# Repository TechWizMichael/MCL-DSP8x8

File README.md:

# MCL-DSP8x8
## Description
Audio Signal Processor based on ESP32-S3 and ADAU1452.

## Goals
+ Eight channels of analog audio input and output
+ Compatibility with "12V" automotive systems
  + As of v0.8 PCB, the device is powered using USB, so 12V operation will require an external USB or 5V power converter.
+ WIP: Remote control through ESP32 (Serial and basic controls through BLE).
+ WIP: Download and upload of settings to restore after flashing new firmware.

## Current State of Firmware
+ Bit of a mess. It's been changing as I've been messing with testing.
+ USB programming of ESP32 is functional.
+ ESP32 successfully programs ADAU1452 and AK4619VN.
+ Bluetooth functionality was briefly tested, with a generic BLE app on android controlling output gain.
+ Can choose between default and custom DSP program by commenting/uncommenting a line in the main .INO file.
  + Default DSP is linear mapping (pass-through) of input to output until ESP32 updates settings after flashing.
    + Defualt will be guaranteed to be compatible with remote control.
      + For this reason, it is highly recommended that the default DSP project, code, and headers remain unchanged.
  + Custom DSP is provided example with registers and input/outputs correctly mapped to physical connections.
    + The Custom DSP program can be modified, but will not offer remote control through the ESP32.
    + The Custom DSP "example" in this repository will likely be whatever I programmed last with it.

## Current state of hardware
### v0.8 (In Testing)
- Important: Buttons are connected incorrectly so they behave as though they are permanently pressed.
  - Removing the buttons or not getting them placed will fix the issue, but the relevant pins may need to be shorted for first-time flashing firmware.
- Using passive attenuation, input range can be expanded.
  - For example, a voltage divider consisting of 47k and 5.6k can be used to achieve 20dB attenuation.
- Analog inputs and outputs use pinheaders with 5 pins with 2.54mm pitch.
  - Each connector carries a differential/balanced connection for two channels.
  - GND, A+, A-, B+, B-
- Similar connectors offer connection to Multi-purpose and AUXADC pins on ADAU1452.
- All appears to be functional with minimal noise
- Measurements:
  - Measured Maximum output (10% THD): 0.939 Vrms (+1.7 dBu)
  - Measured Maximum output (1% THD): 0.814 Vrms (+0.4 dBu)
  - Measured Maximum Input (10% THD): 1.27 Vrms (+4.3 dBu) - Note: potentially my USB interface clipping at 1.28V
  - Measured maximum input (1% THD): 1 Vrms (+2.2dBu)

### Preview of v0.8 from JLCPCB

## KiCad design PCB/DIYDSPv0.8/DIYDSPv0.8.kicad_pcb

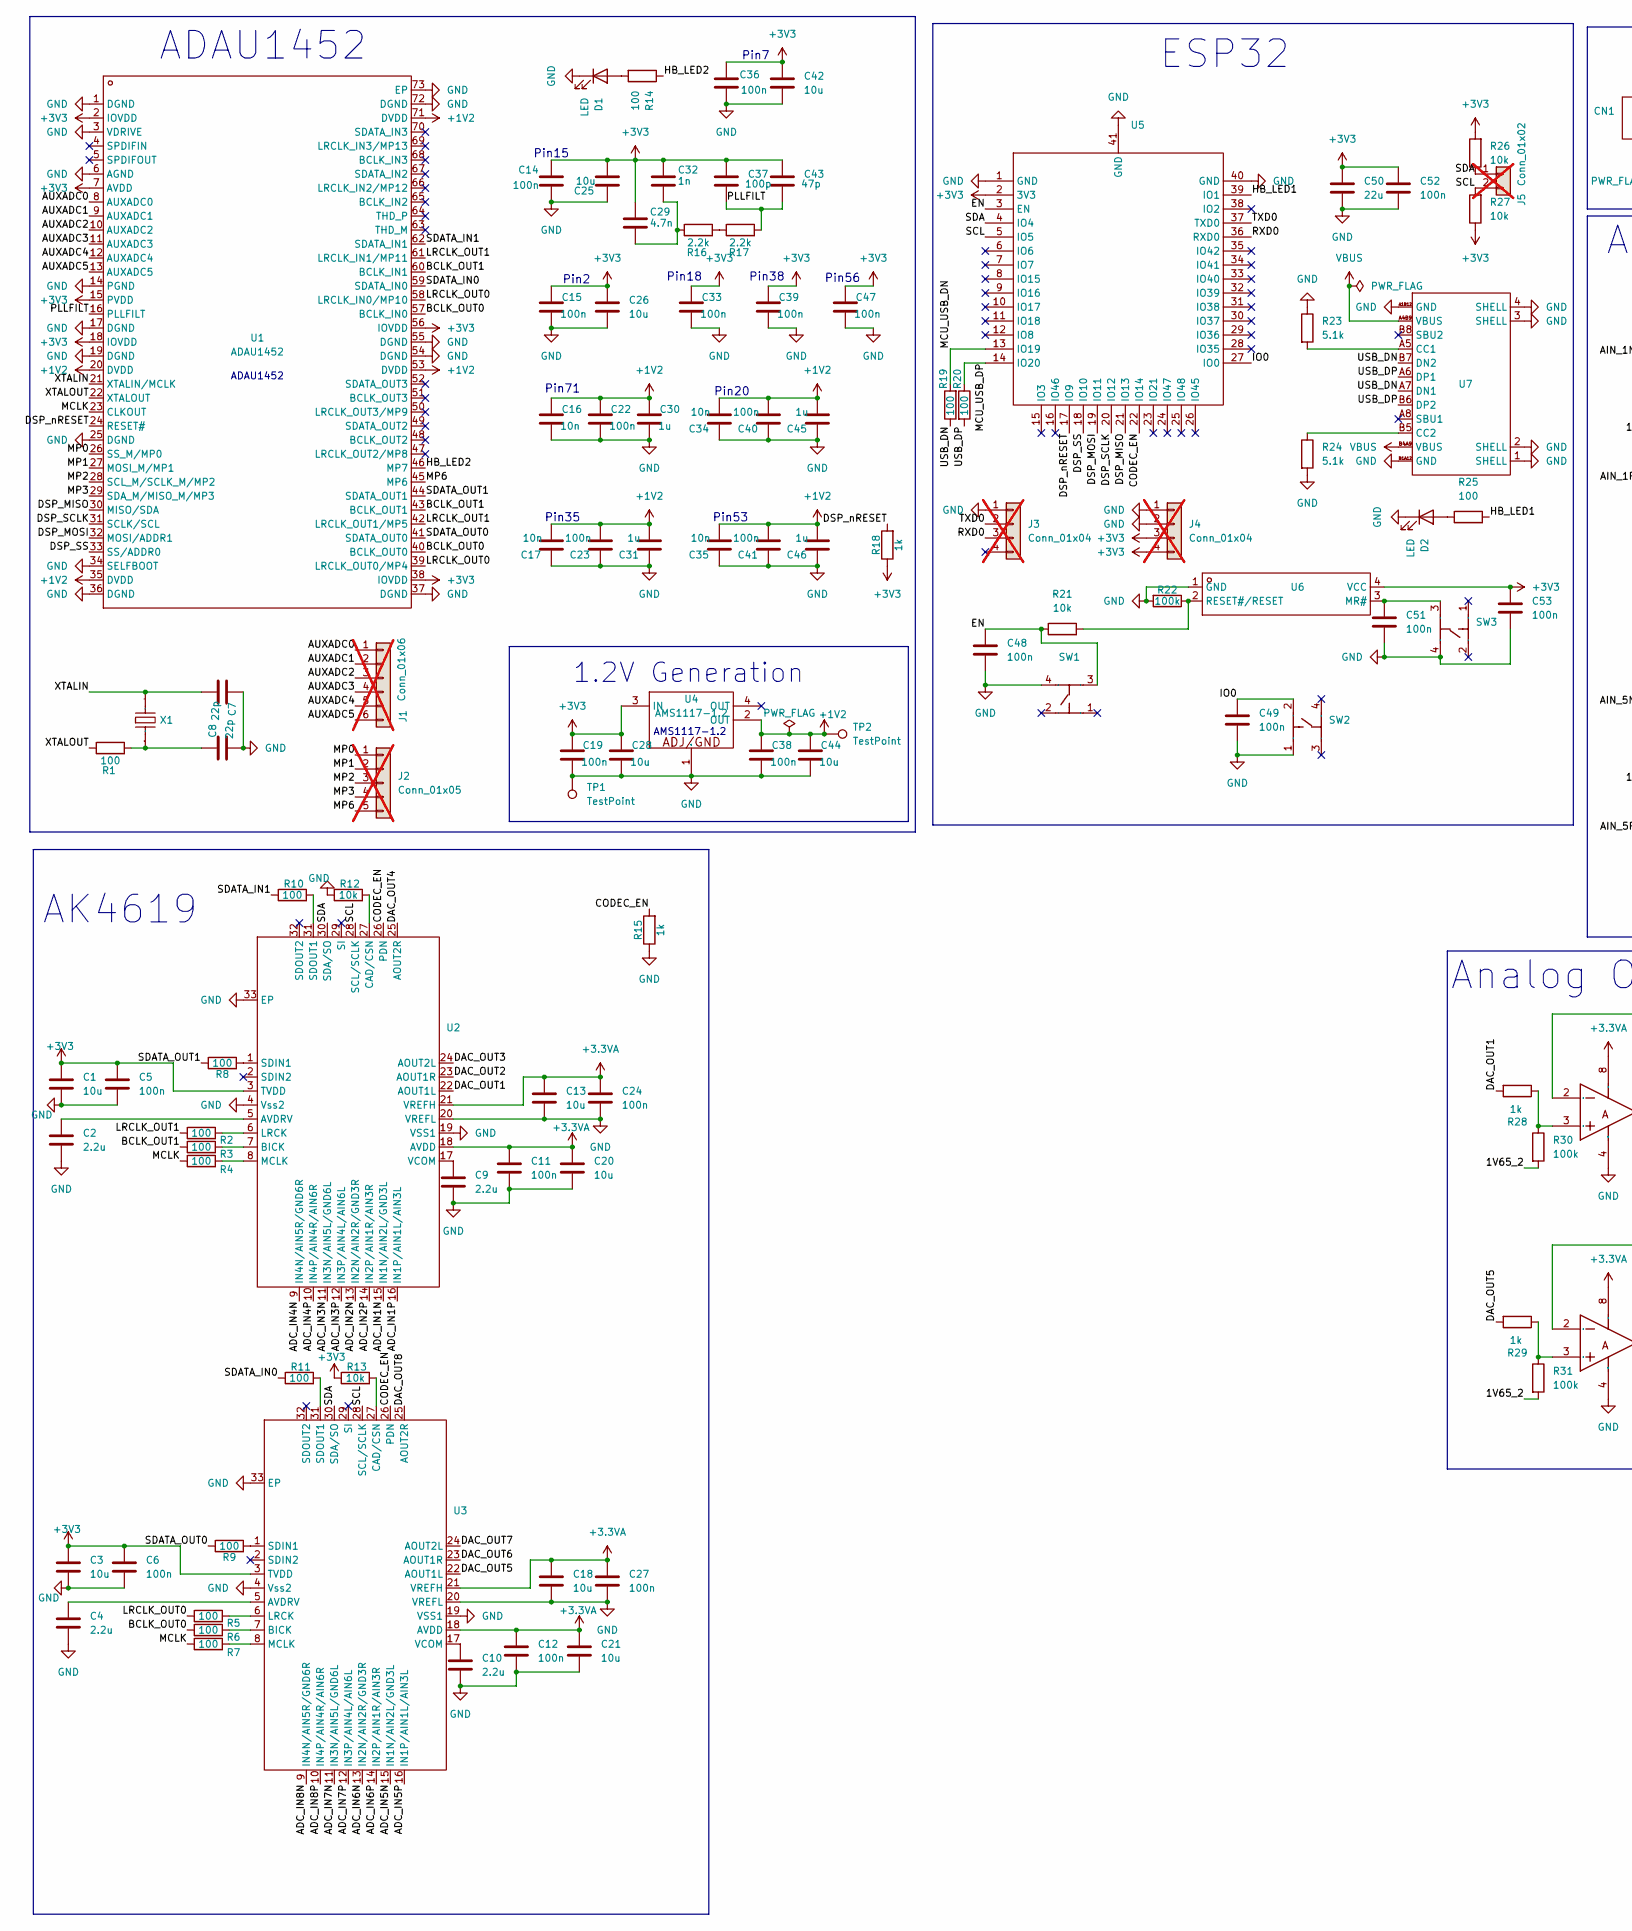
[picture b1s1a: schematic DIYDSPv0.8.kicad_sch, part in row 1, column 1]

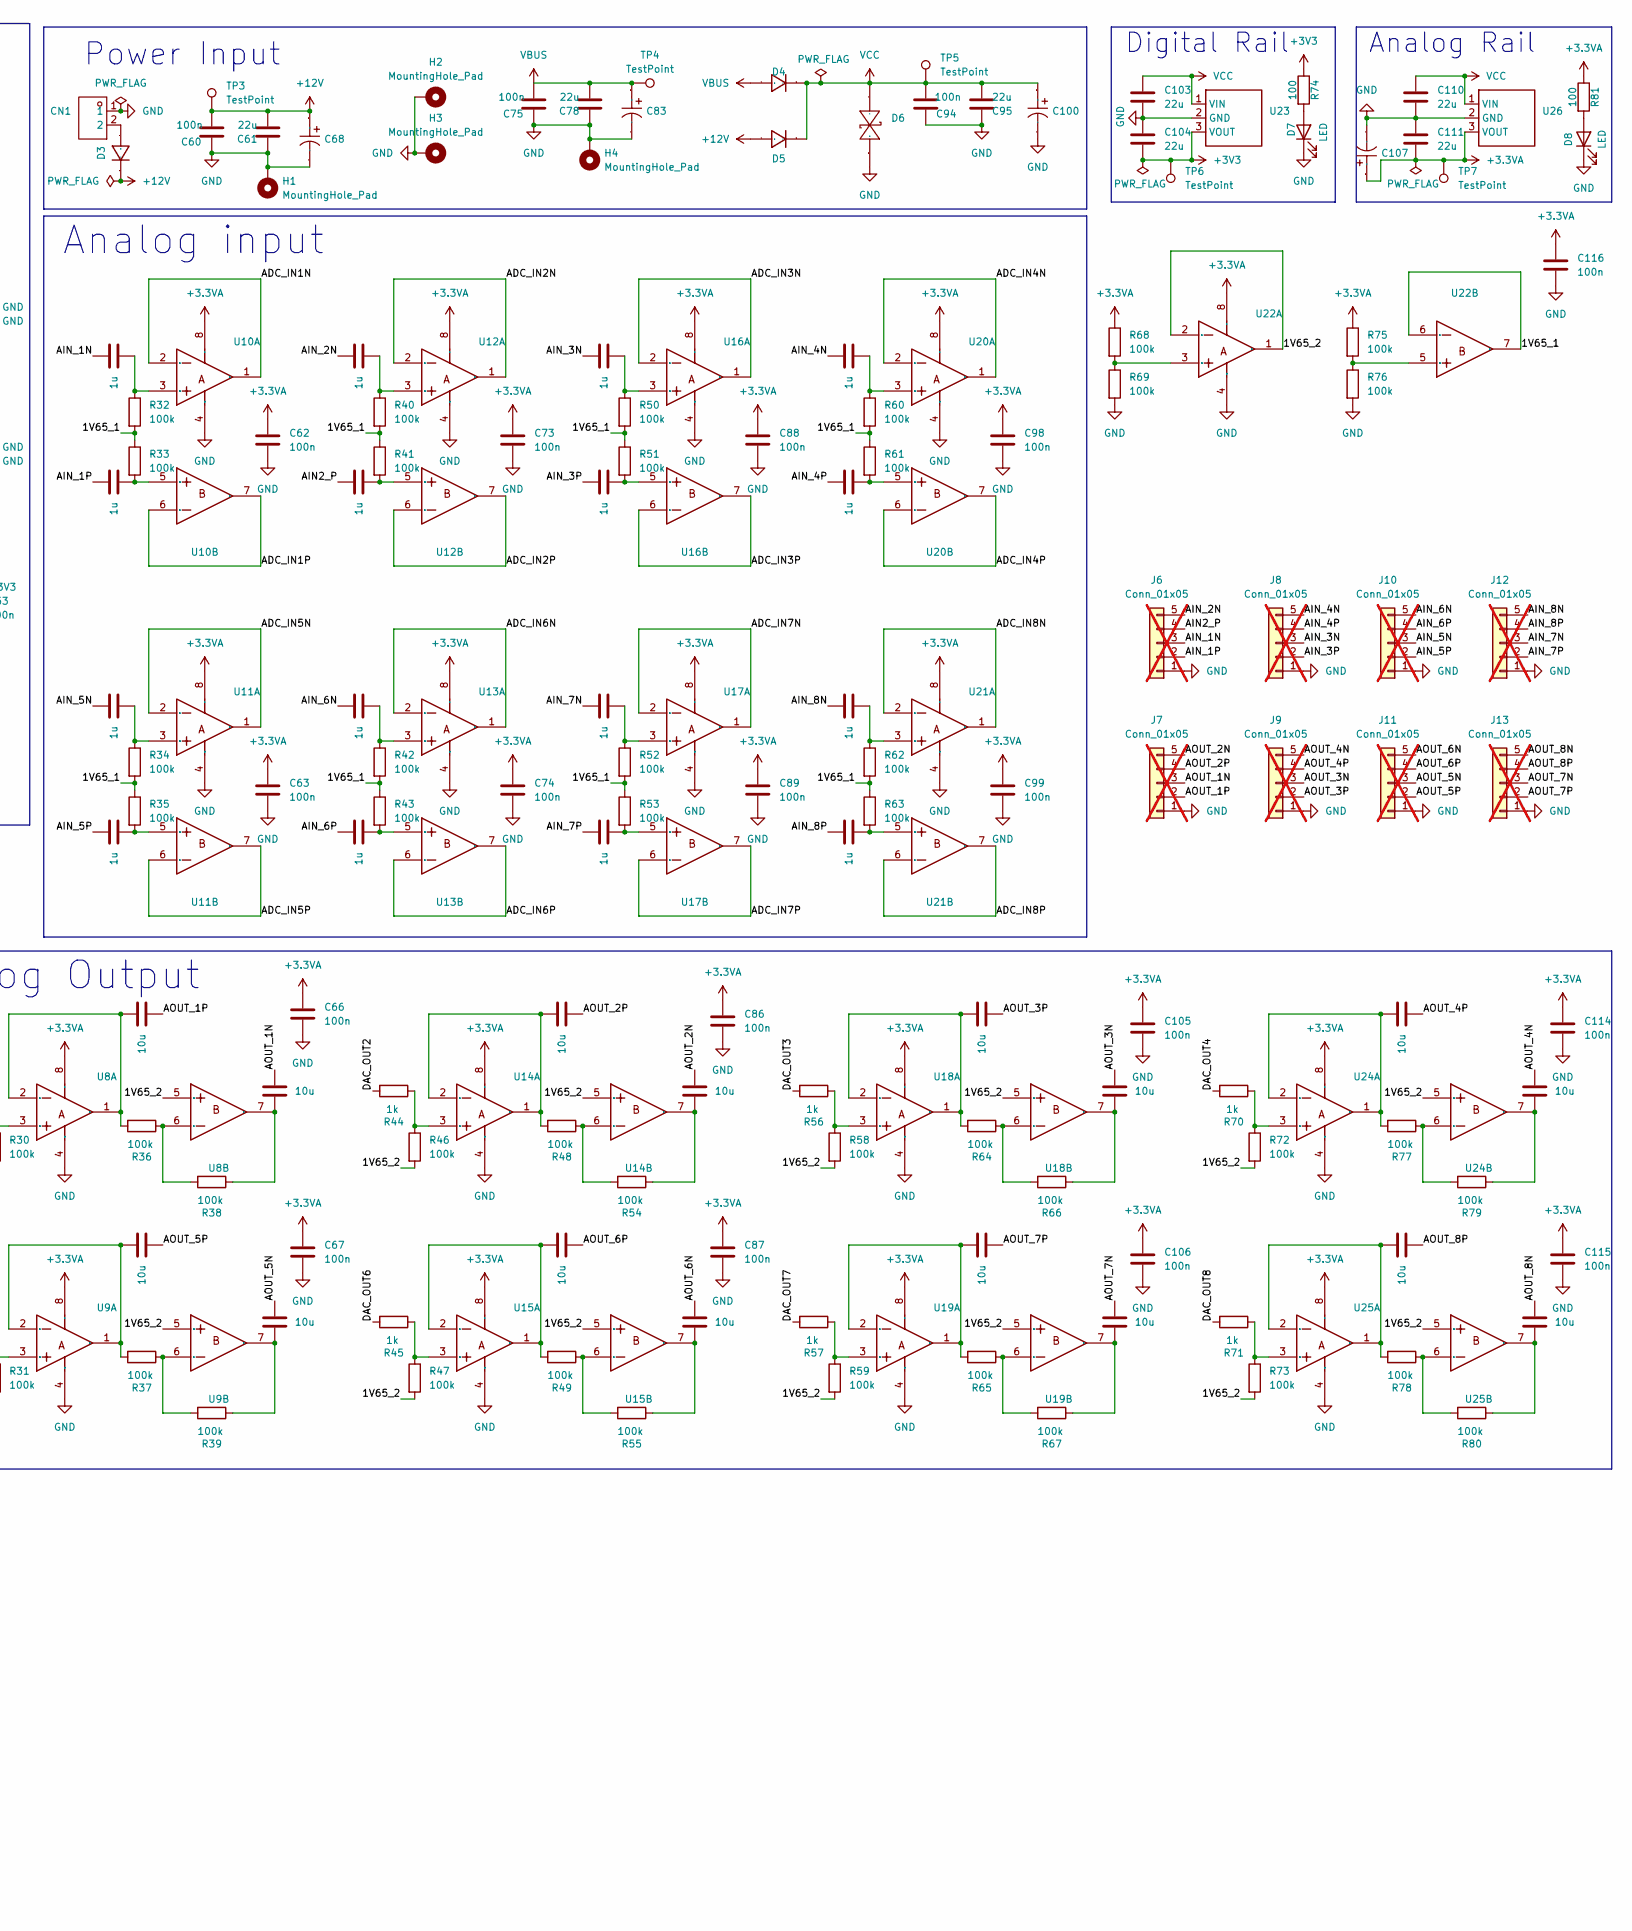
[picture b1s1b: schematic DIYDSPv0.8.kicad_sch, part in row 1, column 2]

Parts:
C1, C3, C13, C18, C20, C21, C25, C26, C28, C42, C44, C58, C59, C64, C65, C76, C77, C84, C85, C96, C97, C101, C102, C108, C109, C112, C113: 10u; C_0603_1608Metric; LCSC Part # C96446
C2, C4, C9, C10: 2.2u; C_0402_1005Metric; LCSC Part # C12530
C5, C6, C11, C12, C14, C15, C19, C22, C23, C24, C27, C33, C36, C38, C39, C40, C41, C47, C48, C49, C51, C52, C53, C60, C62, C63, C66, C67, C73, C74, C75, C86, C87, C88, C89, C94, C98, C99, C105, C106, C114, C115, C116: 100n; C_0402_1005Metric; LCSC Part # C307331
C7, C8: 22p; C_0402_1005Metric; LCSC Part # C1555
C16, C17, C34, C35: 10n; C_0402_1005Metric; LCSC Part # C15195
C29: 4.7n; C_0402_1005Metric; LCSC Part # C1538
C30, C31, C45, C46, C54, C55, C56, C57, C69, C70, C71, C72, C79, C80, C81, C82, C90, C91, C92, C93: 1u; C_0402_1005Metric; LCSC Part # C52923
C32: 1n; C_0402_1005Metric; LCSC Part # C1523
C37: 100p; C_0402_1005Metric; LCSC Part # C1546
C43: 47p; C_0402_1005Metric; LCSC Part # C1567
C50, C61, C78, C95, C103, C104, C110, C111: 22u; C_0805_2012Metric; LCSC Part # C45783
C68, C83, C100, C107: 220uF; RVT1V221M0810; Manufacturer Part RVT1V221M0810; LCSC Part Name 220uF ±20% 35V
CN1: MX126-5.0-02P-GN01-Cu-S-A; Manufacturer Part MX126-5.0-02P-GN01-Cu-S-A; LCSC Part Name 1x2P 5mm 直插 排数:1 每排P数:2
D1, D2, D7, D8: LED; LED_0805_2012Metric; LCSC Part # C84256
D3, D4, D5: CUS08F30,H3F; Manufacturer Part CUS08F30,H3F; LCSC Part Name 电压:30V 电流:800mA
D6: SMF20CA; Manufacturer Part SMF20CA; LCSC Part Name 双向TVS 20V截止 峰值浪涌电流：6.2A
H1, H2, H3, H4: MountingHole_Pad; MountingHole_3.2mm_M3_Pad_TopBottom
J1: Conn_01x06; PinHeader_1x06_P2.54mm_Vertical; not fitted
J2, J6, J7, J8, J9, J10, J11, J12, J13: Conn_01x05; PinHeader_1x05_P2.54mm_Vertical; not fitted
J3, J4: Conn_01x04; PinHeader_1x04_P2.54mm_Vertical; not fitted
J5: Conn_01x02; PinHeader_1x02_P2.54mm_Vertical; not fitted
R1, R2, R3, R4, R5, R6, R7, R8, R9, R10, R11, R14, R19, R20, R25, R74, R81: 100; R_0805_2012Metric; LCSC Part # C17408
R12, R13, R21, R26, R27: 10k; R_0402_1005Metric; LCSC Part # C25744
R15, R18, R28, R29, R44, R45, R56, R57, R70, R71: 1k; R_0402_1005Metric; LCSC Part # C11702
R16, R17: 2.2k; R_0402_1005Metric; LCSC Part # C25879
R22, R30, R31, R32, R33, R34, R35, R36, R37, R38, R39, R40, R41, R42, R43, R46, R47, R48, R49, R50, R51, R52, R53, R54, R55, R58, R59, R60, R61, R62, R63, R64, R65, R66, R67, R68, R69, R72, R73, R75, R76, R77, R78, R79, R80: 100k; R_0402_1005Metric; LCSC Part # C25741
R23, R24: 5.1k; R_0402_1005Metric; LCSC Part # C25905
SW1, SW2, SW3: TS110916043; Manufacturer Part TS110916043; LCSC Part Name TS110916043
TP1: TestPoint; TestPoint_THTPad_D4.0mm_Drill2.0mm
TP2, TP3, TP4, TP5, TP6, TP7: TestPoint; TestPoint_THTPad_D2.0mm_Drill1.0mm
U1: ADAU1452; ADAU1452WBCPZ-RL; Manufacturer Part ADAU1452WBCPZ-RL; LCSC Part Name SigmaDSP 数字音频处理器
U2, U3: AK4619VN; Manufacturer Part AK4619VN; LCSC Part Name AK4619VN
U4: AMS1117-1.2; Manufacturer Part AMS1117-1.2; LCSC Part Name 1.2V 1A 15V
U5: ESP32-S3-WROOM-1U-N8; Manufacturer Part ESP32-S3-WROOM-1U-N8; LCSC Part Name 通用型Wi-Fi+低功耗蓝牙MCU模组
U6: ADM811TARTZ-REEL7; Manufacturer Part ADM811TARTZ-REEL7; LCSC Part Name 4引脚SOT-143微处理器监控电路
U7: GT-USB-7010ASV; Manufacturer Part GT-USB-7010ASV; LCSC Part Name Type-C 母 卧贴
U8, U9, U10, U11, U12, U13, U14, U15, U16, U17, U18, U19, U20, U21, U22, U24, U25: TLV9062IDR; Manufacturer Part TLV9062IDR; LCSC Part Name 适用于成本敏感型系统的10MHz、轨到轨输入输出（RRIO）CMOS运算放大器
U23, U26: K7803-1000_C50396471; Manufacturer Part K7803-1000; LCSC Part Name DC-DC模块电源，宽电压输入，非隔离稳压单路输出
X1: 12.288MHz; S47SMD12.288M20PF20R30B3; Manufacturer Part S47SMD12.288M20PF20R30B3; LCSC Part Name 12.288MHz ±20ppm 20pF

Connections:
+1V2: C16.1, C17.2, C22.1, C23.2, C30.1, C31.2, C34.2, C35.2, C38.1, C40.2, C41.2, C44.1, C45.2, C46.2, TP2.1, U1.20 (DVDD), U1.35 (DVDD), U1.53 (DVDD), U1.71 (DVDD), U4.2 (OUT)
+3V3: C1.2, C3.2, C5.2, C6.2, C14.1, C15.1, C19.1, C25.2, C26.1, C28.1, C29.1, C32.1, C33.1, C36.1, C37.1, C39.1, C42.1, C43.1, C47.1, C50.1, C52.1, C53.2, C104.1, J4.3, J4.4, R13.1, R18.1, R26.2, R27.1, R74.1, TP6.1, U1.2 (IOVDD), U1.7 (AVDD), U1.15 (PVDD), U1.18 (IOVDD), U1.38 (IOVDD), U1.56 (IOVDD), U2.3 (TVDD), U3.3 (TVDD), U4.3 (IN), U5.2 (3V3), U6.4 (VCC), U23.3 (VOUT); also elsewhere on the board
/1V65_1: R32.2, R33.1, R34.2, R35.1, R40.2, R41.1, R42.2, R43.1, R50.2, R51.1, R52.2, R53.1, R60.2, R61.1, R62.2, R63.1, U22.6 (INB-), U22.7 (OUTB)
/1V65_2: R30.2, R31.2, R46.2, R47.2, R58.2, R59.2, R72.2, R73.2, U8.5 (INB+), U9.5 (INB+), U14.5 (INB+), U15.5 (INB+), U18.5 (INB+), U19.5 (INB+), U22.1 (OUTA), U22.2 (INA-), U24.5 (INB+), U25.5 (INB+)
/ADC_IN1N: U2.15 (IN1N/AIN2L/GND3L), U10.1 (OUTA), U10.2 (INA-)
/ADC_IN1P: U2.16 (IN1P/AIN1L/AIN3L), U10.6 (INB-), U10.7 (OUTB)
/ADC_IN2N: U2.13 (IN2N/AIN2R/GND3R), U12.1 (OUTA), U12.2 (INA-)
/ADC_IN2P: U2.14 (IN2P/AIN1R/AIN3R), U12.6 (INB-), U12.7 (OUTB)
/ADC_IN3N: U2.11 (IN3N/AIN5L/GND6L), U16.1 (OUTA), U16.2 (INA-)
/ADC_IN3P: U2.12 (IN3P/AIN4L/AIN6L), U16.6 (INB-), U16.7 (OUTB)
/ADC_IN4N: U2.9 (IN4N/AIN5R/GND6R), U20.1 (OUTA), U20.2 (INA-)
/ADC_IN4P: U2.10 (IN4P/AIN4R/AIN6R), U20.6 (INB-), U20.7 (OUTB)
/ADC_IN5N: U3.15 (IN1N/AIN2L/GND3L), U11.1 (OUTA), U11.2 (INA-)
/ADC_IN5P: U3.16 (IN1P/AIN1L/AIN3L), U11.6 (INB-), U11.7 (OUTB)
/ADC_IN6N: U3.13 (IN2N/AIN2R/GND3R), U13.1 (OUTA), U13.2 (INA-)
/ADC_IN6P: U3.14 (IN2P/AIN1R/AIN3R), U13.6 (INB-), U13.7 (OUTB)
/ADC_IN7N: U3.11 (IN3N/AIN5L/GND6L), U17.1 (OUTA), U17.2 (INA-)
/ADC_IN7P: U3.12 (IN3P/AIN4L/AIN6L), U17.6 (INB-), U17.7 (OUTB)
/ADC_IN8N: U3.9 (IN4N/AIN5R/GND6R), U21.1 (OUTA), U21.2 (INA-)
/ADC_IN8P: U3.10 (IN4P/AIN4R/AIN6R), U21.6 (INB-), U21.7 (OUTB)
/AIN2_P: C70.2, J6.4
/AIN_1N: C54.2, J6.3
/AIN_1P: C55.2, J6.2
/AIN_2N: C69.2, J6.5
/AIN_3N: C79.2, J8.3
/AIN_3P: C80.2, J8.2
/AIN_4N: C90.2, J8.5
/AIN_4P: C91.2, J8.4
/AIN_5N: C56.2, J10.3
/AIN_5P: C57.2, J10.2
/AIN_6N: C71.2, J10.5
/AIN_6P: C72.2, J10.4
/AIN_7N: C81.2, J12.3
/AIN_7P: C82.2, J12.2
/AIN_8N: C92.2, J12.5
/AIN_8P: C93.2, J12.4
/AOUT_1N: C64.1, J7.3
/AOUT_1P: C58.1, J7.2
/AOUT_2N: C84.1, J7.5
/AOUT_2P: C76.1, J7.4
/AOUT_3N: C101.1, J9.3
/AOUT_3P: C96.1, J9.2
/AOUT_4N: C112.1, J9.5
/AOUT_4P: C108.1, J9.4
/AOUT_5N: C65.1, J11.3
/AOUT_5P: C59.1, J11.2
/AOUT_6N: C85.1, J11.5
/AOUT_6P: C77.1, J11.4
/AOUT_7N: C102.1, J13.3
/AOUT_7P: C97.1, J13.2
/AOUT_8N: C113.1, J13.5
/AOUT_8P: C109.1, J13.4
/AUXADC0: J1.1, U1.8 (AUXADC0)
/AUXADC1: J1.2, U1.9 (AUXADC1)
/AUXADC2: J1.3, U1.10 (AUXADC2)
/AUXADC3: J1.4, U1.11 (AUXADC3)
/AUXADC4: J1.5, U1.12 (AUXADC4)
/AUXADC5: J1.6, U1.13 (AUXADC5)
/BCLK_OUT0: R6.1, U1.40 (BCLK_OUT0), U1.57 (BCLK_IN0)
/BCLK_OUT1: R3.1, U1.43 (BCLK_OUT1), U1.60 (BCLK_IN1)
/CODEC_EN: R15.2, U2.26 (PDN), U3.26 (PDN), U5.22 (IO14)
/DAC_OUT1: R28.2, U2.22 (AOUT1L)
/DAC_OUT2: R44.2, U2.23 (AOUT1R)
/DAC_OUT3: R56.2, U2.24 (AOUT2L)
/DAC_OUT4: R70.2, U2.25 (AOUT2R)
/DAC_OUT5: R29.2, U3.22 (AOUT1L)
/DAC_OUT6: R45.2, U3.23 (AOUT1R)
/DAC_OUT7: R57.2, U3.24 (AOUT2L)
/DAC_OUT8: R71.2, U3.25 (AOUT2R)
/DSP_MISO: U1.30 (MISO/SDA), U5.21 (IO13)
/DSP_MOSI: U1.32 (MOSI/ADDR1), U5.19 (IO11)
/DSP_SCLK: U1.31 (SCLK/SCL), U5.20 (IO12)
/DSP_SS: U1.33 (SS/ADDR0), U5.18 (IO10)
/DSP_nRESET: R18.2, U1.24 (RESET#), U5.17 (IO9)
/EN: C48.1, R21.1, SW1.3, U5.3 (EN)
/HB_LED1: R25.2, U5.39 (IO1)
/HB_LED2: R14.1, U1.46 (MP7)
/IO0: C49.2, SW2.2, U5.27 (IO0)
/LRCLK_OUT0: R5.1, U1.39 (LRCLK_OUT0/MP4), U1.58 (LRCLK_IN0/MP10)
/LRCLK_OUT1: R2.1, U1.42 (LRCLK_OUT1/MP5), U1.61 (LRCLK_IN1/MP11)
/MCLK: R4.1, R7.1, U1.23 (CLKOUT)
/MCU_USB_DN: R19.2, U5.13 (IO19)
/MCU_USB_DP: R20.1, U5.14 (IO20)
/MP0: J2.1, U1.26 (SS_M/MP0)
/MP1: J2.2, U1.27 (MOSI_M/MP1)
/MP2: J2.3, U1.28 (SCL_M/SCLK_M/MP2)
/MP3: J2.4, U1.29 (SDA_M/MISO_M/MP3)
/MP6: J2.5, U1.45 (MP6)
/PLLFILT: C37.2, C43.2, R17.2, U1.16 (PLLFILT)
/RXD0: J3.3, U5.36 (RXD0)
/SCL: J5.2, R27.2, U2.28 (SCL/SCLK), U3.28 (SCL/SCLK), U5.5 (IO5)
/SDA: J5.1, R26.1, U2.30 (SDA/SO), U3.30 (SDA/SO), U5.4 (IO4)
/SDATA_IN0: R11.1, U1.59 (SDATA_IN0)
/SDATA_IN1: R10.1, U1.62 (SDATA_IN1)
/SDATA_OUT0: R9.1, U1.41 (SDATA_OUT0)
/SDATA_OUT1: R8.1, U1.44 (SDATA_OUT1)
/TXD0: J3.2, U5.37 (TXD0)
/USB_DN: R19.1, U7.A7 (DN1), U7.B7 (DN2)
/USB_DP: R20.2, U7.A6 (DP1), U7.B6 (DP2)
/XTALIN: C7.2, U1.21 (XTALIN/MCLK), X1.2
/XTALOUT: R1.1, U1.22 (XTALOUT)
unnamed: C8.1, R1.2, X1.1
unnamed: C29.2, C32.2, R16.1
unnamed: D1.2 (A), R14.2
unnamed: D2.2 (A), R25.1
unnamed: D7.2 (A), R74.2
unnamed: D8.2 (A), R81.2
unnamed: R16.2, R17.1
unnamed: C2.2, U2.5 (AVDRV)
unnamed: R3.2, U2.7 (BICK)
unnamed: R12.2, U2.27 (CAD/CSN)
unnamed: R2.2, U2.6 (LRCK)
unnamed: R4.2, U2.8 (MCLK)
unnamed: R8.2, U2.1 (SDIN1)
unnamed: R10.2, U2.31 (SDOUT1)
unnamed: C9.2, U2.17 (VCOM)
unnamed: C4.2, U3.5 (AVDRV)
unnamed: R6.2, U3.7 (BICK)
unnamed: R13.2, U3.27 (CAD/CSN)
unnamed: R5.2, U3.6 (LRCK)
unnamed: R7.2, U3.8 (MCLK)
unnamed: R9.2, U3.1 (SDIN1)
unnamed: R11.2, U3.31 (SDOUT1)
unnamed: C10.2, U3.17 (VCOM)
unnamed: C51.1, SW3.3, U6.3 (MR#)
unnamed: R21.2, R22.1, U6.2 (RESET#/RESET)
unnamed: R23.2, U7.A5 (CC1)
unnamed: R24.1, U7.B5 (CC2)
unnamed: R28.1, R30.1, U8.3 (INA+)
unnamed: C58.2, R36.2, U8.1 (OUTA), U8.2 (INA-)
unnamed: R36.1, R38.2, U8.6 (INB-)
unnamed: C64.2, R38.1, U8.7 (OUTB)
unnamed: R29.1, R31.1, U9.3 (INA+)
unnamed: C59.2, R37.2, U9.1 (OUTA), U9.2 (INA-)
unnamed: R37.1, R39.2, U9.6 (INB-)
unnamed: C65.2, R39.1, U9.7 (OUTB)
unnamed: C54.1, R32.1, U10.3 (INA+)
unnamed: C55.1, R33.2, U10.5 (INB+)
unnamed: C56.1, R34.1, U11.3 (INA+)
unnamed: C57.1, R35.2, U11.5 (INB+)
unnamed: C69.1, R40.1, U12.3 (INA+)
unnamed: C70.1, R41.2, U12.5 (INB+)
unnamed: C71.1, R42.1, U13.3 (INA+)
unnamed: C72.1, R43.2, U13.5 (INB+)
unnamed: R44.1, R46.1, U14.3 (INA+)
unnamed: C76.2, R48.2, U14.1 (OUTA), U14.2 (INA-)
unnamed: R48.1, R54.2, U14.6 (INB-)
unnamed: C84.2, R54.1, U14.7 (OUTB)
unnamed: R45.1, R47.1, U15.3 (INA+)
unnamed: C77.2, R49.2, U15.1 (OUTA), U15.2 (INA-)
unnamed: R49.1, R55.2, U15.6 (INB-)
unnamed: C85.2, R55.1, U15.7 (OUTB)
unnamed: C79.1, R50.1, U16.3 (INA+)
unnamed: C80.1, R51.2, U16.5 (INB+)
unnamed: C81.1, R52.1, U17.3 (INA+)
unnamed: C82.1, R53.2, U17.5 (INB+)
unnamed: R56.1, R58.1, U18.3 (INA+)
unnamed: C96.2, R64.2, U18.1 (OUTA), U18.2 (INA-)
unnamed: R64.1, R66.2, U18.6 (INB-)
unnamed: C101.2, R66.1, U18.7 (OUTB)
unnamed: R57.1, R59.1, U19.3 (INA+)
unnamed: C97.2, R65.2, U19.1 (OUTA), U19.2 (INA-)
unnamed: R65.1, R67.2, U19.6 (INB-)
unnamed: C102.2, R67.1, U19.7 (OUTB)
unnamed: C90.1, R60.1, U20.3 (INA+)
unnamed: C91.1, R61.2, U20.5 (INB+)
unnamed: C92.1, R62.1, U21.3 (INA+)
unnamed: C93.1, R63.2, U21.5 (INB+)
unnamed: R68.2, R69.1, U22.3 (INA+)
unnamed: R75.2, R76.1, U22.5 (INB+)
unnamed: R70.1, R72.1, U24.3 (INA+)
unnamed: C108.2, R77.2, U24.1 (OUTA), U24.2 (INA-)
unnamed: R77.1, R79.2, U24.6 (INB-)
unnamed: C112.2, R79.1, U24.7 (OUTB)
unnamed: R71.1, R73.1, U25.3 (INA+)
unnamed: C109.2, R78.2, U25.1 (OUTA), U25.2 (INA-)
unnamed: R78.1, R80.2, U25.6 (INB-)
unnamed: C113.2, R80.1, U25.7 (OUTB)
unnamed 178: U26.A5 (CC1); also elsewhere on the board
unnamed 179: U26.B5 (CC2); also elsewhere on the board
VBUS: C75.2, C78.2, C83.1, D4.2 (A), TP4.1, U7.A4B9 (VBUS), U7.B4A9 (VBUS)
VBUS2: CN1.2, D3.2 (A), U26.A4B9 (VBUS), U26.B4A9 (VBUS)

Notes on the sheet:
Analog input
Pin15
Pin56
ESP32
ADAU1452
Pin7
Pin53
Analog Rail
1.2V Generation
Pin20
AMS1117-1.2
Pin35
Pin2
Pin18
Analog Output
AK4619
Power Input
Pin71
Pin38
Digital Rail

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
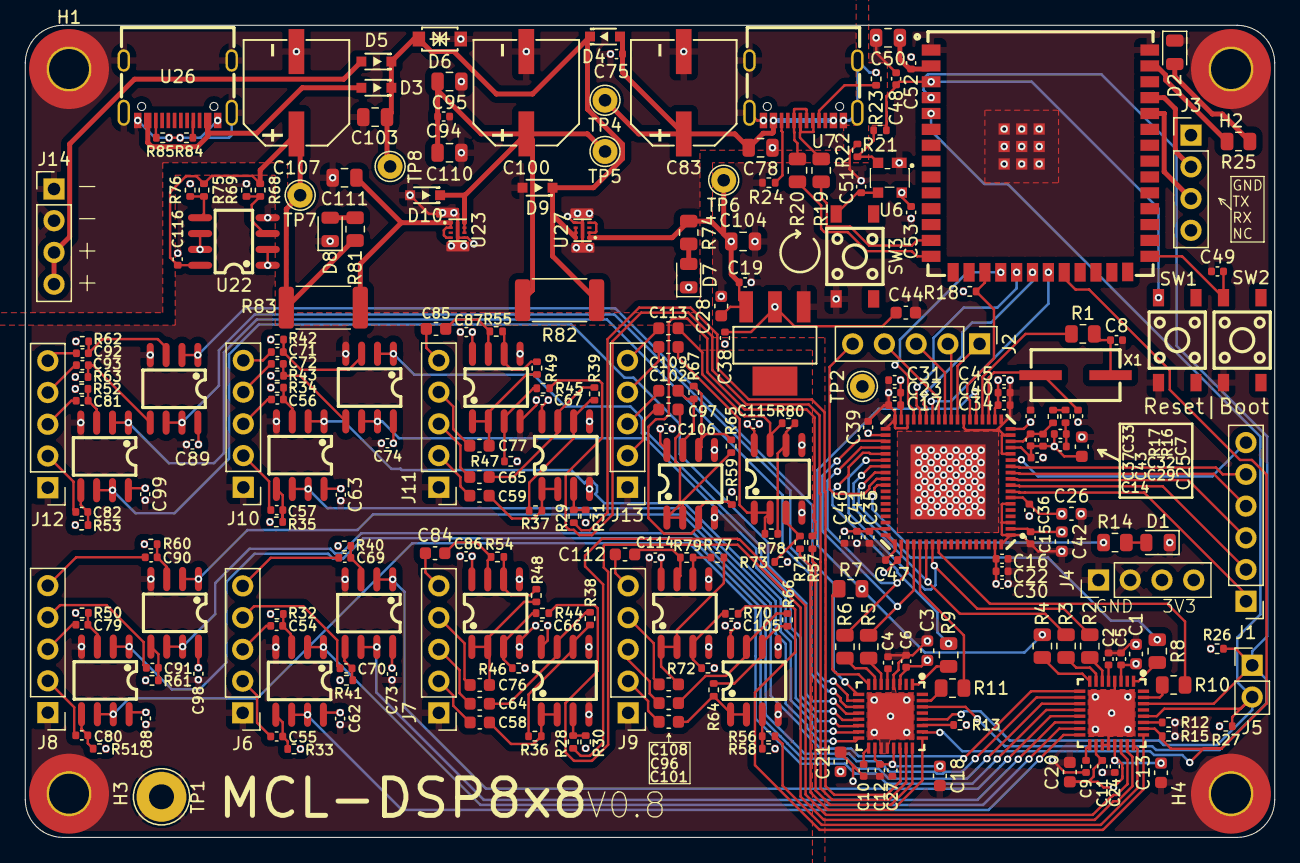
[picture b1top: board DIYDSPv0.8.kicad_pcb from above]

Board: 4 copper layers, 100.0 x 65.0 mm, 264 parts (0 on the bottom side), 188 nets.

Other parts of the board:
D9, D10: DDZ5V6CSF-7
J14: Conn_01x04; PinHeader_1x04_P2.54mm_Vertical
R82, R83: 0.2; R_2512_6332Metric
R84, R85: 5.1k; R_0402_1005Metric
TP8: TestPoint; TestPoint_THTPad_D2.0mm_Drill1.0mm
U27: SGM2039A-3.3XXEV8G_TR

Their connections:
+3V3: U27.1 (OUT), U27.2 (OUT), U27.4 (FB); also elsewhere on the board
unnamed 178: R84.2; also elsewhere on the board
unnamed 179: R85.1; also elsewhere on the board

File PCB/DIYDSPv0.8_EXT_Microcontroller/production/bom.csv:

Designator,Footprint,Quantity,Value,LCSC Part #
"C1, C101, C102, C108, C109, C112, C113, C13, C18, C20, C21, C25, C26, C28, C3, C42, C44, C58, C59, C64, C65, C76, C77, C84, C85, C96, C97",0603,27,10u,C96446
"C10, C2, C4, C9",0402,4,2.2u,C12530
"C100, C107, C68, C83",RVT1V221M0810,4,220uF,C18221522
"C103, C104, C110, C111, C61, C78, C95",0805,7,22u,C45783
"C105, C106, C11, C114, C115, C116, C12, C14, C15, C19, C22, C23, C24, C27, C33, C36, C38, C39, C40, C41, C47, C5, C6, C60, C62, C63, C66, C67, C73, C74, C75, C86, C87, C88, C89, C94, C98, C99",0402,38,100n,C307331
"C16, C17, C34, C35",0402,4,10n,C15195
C29,0402,1,4.7n,C1538
"C30, C31, C45, C46, C54, C55, C56, C57, C69, C70, C71, C72, C79, C80, C81, C82, C90, C91, C92, C93",0402,20,1u,C52923
C32,0402,1,1n,C1523
C37,0402,1,100p,C1546
C43,0402,1,47p,C1567
"C7, C8",0402,2,22p,C1555
CN1,MX126-5.0-02P-GN01-Cu-S-A,1,~,C5188434
"D1, D7, D8",0805,3,LED,C84256
"D3, D4, D5","CUS08F30,H3F",3,~,C150183
D6,SMF20CA,1,~,C42371747
"R1, R10, R11, R14, R2, R3, R4, R5, R6, R7, R74, R8, R81, R9",0805,14,100, C17408
"R12, R13, R26, R27",0402,4,10k,C25744
"R15, R18, R28, R29, R44, R45, R56, R57, R70, R71",0402,10,1k,C11702
"R16, R17",0402,2,2.2k, C25879
"R30, R31, R32, R33, R34, R35, R36, R37, R38, R39, R40, R41, R42, R43, R46, R47, R48, R49, R50, R51, R52, R53, R54, R55, R58, R59, R60, R61, R62, R63, R64, R65, R66, R67, R68, R69, R72, R73, R75, R76, R77, R78, R79, R80",0402,44,100k,C25741
U1,ADAU1452WBCPZ-RL,1,ADAU1452,C462188
"U10, U11, U12, U13, U14, U15, U16, U17, U18, U19, U20, U21, U22, U24, U25, U8, U9",TLV9062IDR,17,~,C398355
"U2, U3",AK4619VN,2,~,C3034747
"U23, U26",K7803-1000_C50396471,2,~,
U4,AMS1117-1.2,1,AMS1117-1.2,C2992568
X1,S47SMD12.288M20PF20R30B3,1,12.288MHz,C5346044

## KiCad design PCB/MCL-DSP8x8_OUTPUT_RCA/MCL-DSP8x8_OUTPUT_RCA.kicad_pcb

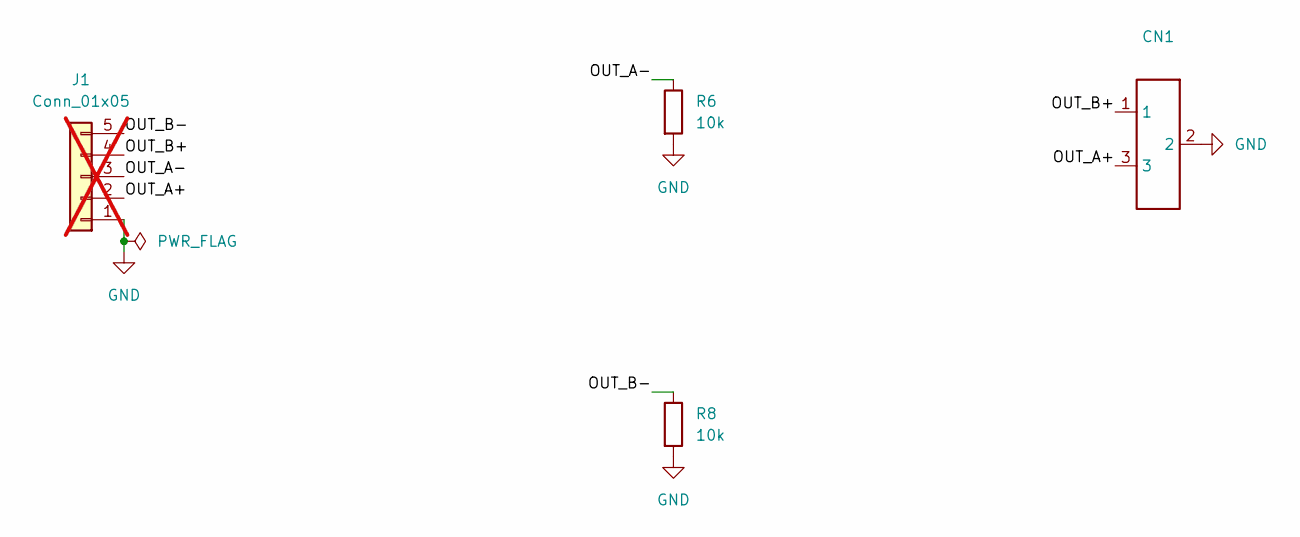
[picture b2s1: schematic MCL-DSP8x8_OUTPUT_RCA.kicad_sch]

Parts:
CN1: XDJK-0271-1650; Manufacturer Part XDJK-0271-1650; LCSC Part Name 双层莲花座
J1: Conn_01x05; PinHeader_1x05_P2.54mm_Vertical; not fitted
R6, R8: 10k; R_0805_2012Metric_Pad1.20x1.40mm_HandSolder; LCSC Part # C3152175

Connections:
/OUT_A+: CN1.3, J1.2
/OUT_A-: J1.3, R6.1
/OUT_B+: CN1.1, J1.4
/OUT_B-: J1.5, R8.1
GND: CN1.2, J1.1, R6.2, R8.2

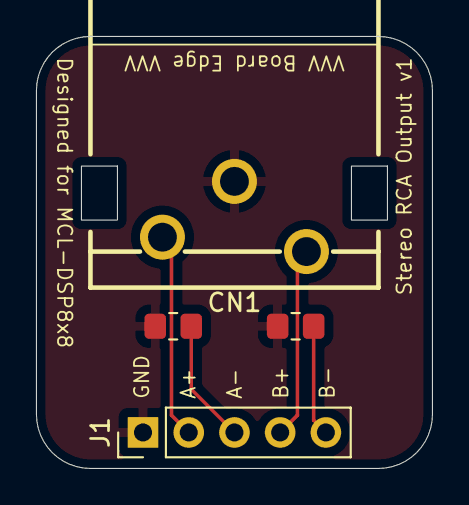
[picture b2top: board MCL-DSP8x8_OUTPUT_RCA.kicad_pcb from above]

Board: 2 copper layers, 22.0 x 24.0 mm, 4 parts (0 on the bottom side), 5 nets.

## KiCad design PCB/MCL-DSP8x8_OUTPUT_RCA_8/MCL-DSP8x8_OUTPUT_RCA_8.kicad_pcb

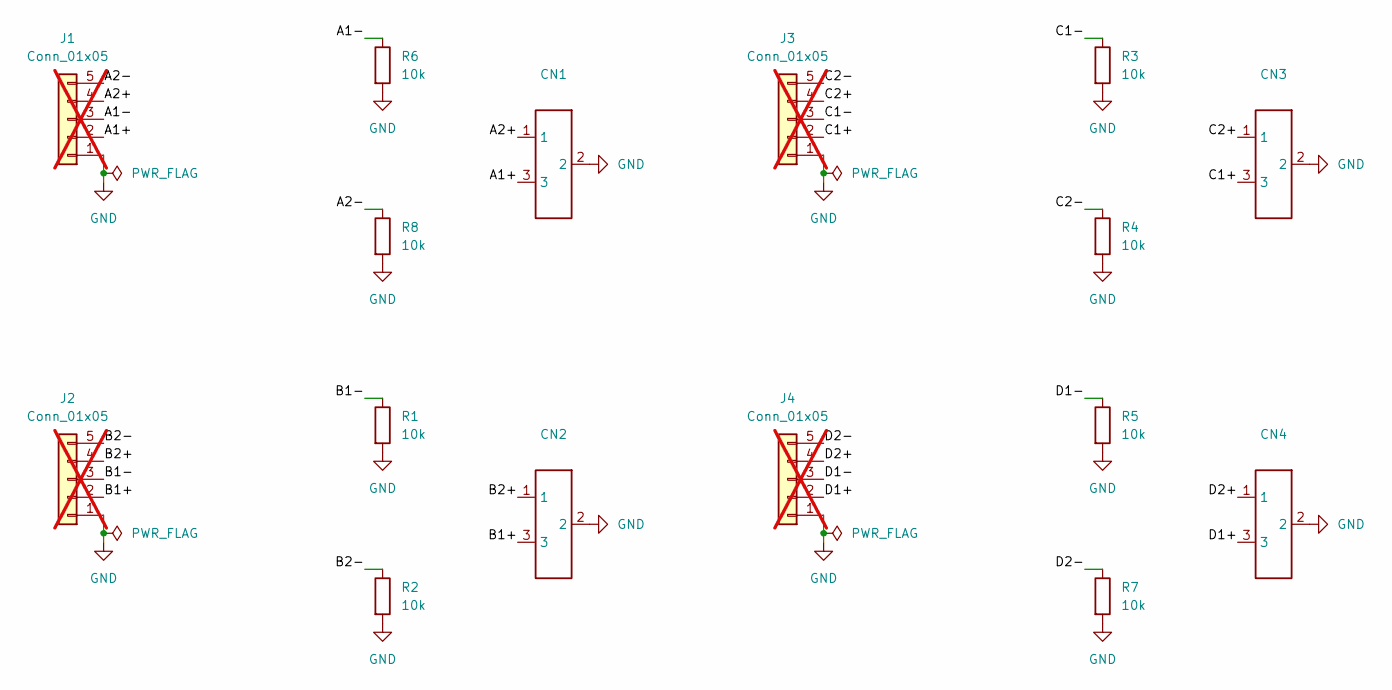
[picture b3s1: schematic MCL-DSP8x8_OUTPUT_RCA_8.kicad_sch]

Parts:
CN1, CN2, CN3, CN4: XDJK-0271-1650; Manufacturer Part XDJK-0271-1650; LCSC Part Name 双层莲花座
J1, J2, J3, J4: Conn_01x05; PinHeader_1x05_P2.54mm_Vertical; not fitted
R1, R2, R3, R4, R5, R6, R7, R8: 10k; R_0805_2012Metric_Pad1.20x1.40mm_HandSolder; LCSC Part # C3152175

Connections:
/A1+: CN1.3, J1.2
/A1-: J1.3, R6.1
/A2+: CN1.1, J1.4
/A2-: J1.5, R8.1
/B1+: CN2.3, J2.2
/B1-: J2.3, R1.1
/B2+: CN2.1, J2.4
/B2-: J2.5, R2.1
/C1+: CN3.3, J3.2
/C1-: J3.3, R3.1
/C2+: CN3.1, J3.4
/C2-: J3.5, R4.1
/D1+: CN4.3, J4.2
/D1-: J4.3, R5.1
/D2+: CN4.1, J4.4
/D2-: J4.5, R7.1
GND: CN1.2, CN2.2, CN3.2, CN4.2, J1.1, J2.1, J3.1, J4.1, R1.2, R2.2, R3.2, R4.2, R5.2, R6.2, R7.2, R8.2

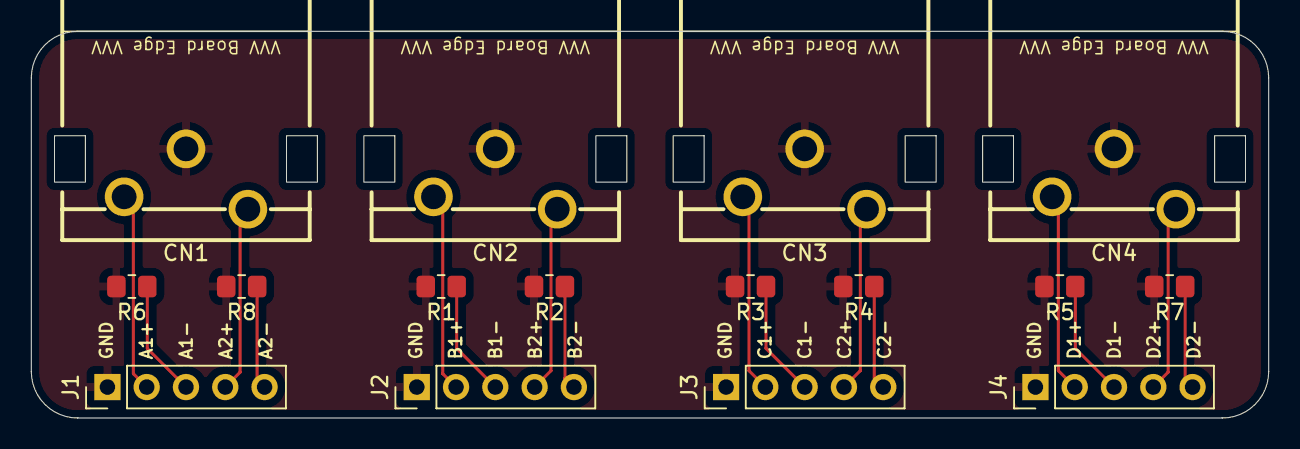
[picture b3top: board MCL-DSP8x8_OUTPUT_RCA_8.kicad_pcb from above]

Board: 2 copper layers, 80.0 x 25.0 mm, 16 parts (0 on the bottom side), 17 nets.

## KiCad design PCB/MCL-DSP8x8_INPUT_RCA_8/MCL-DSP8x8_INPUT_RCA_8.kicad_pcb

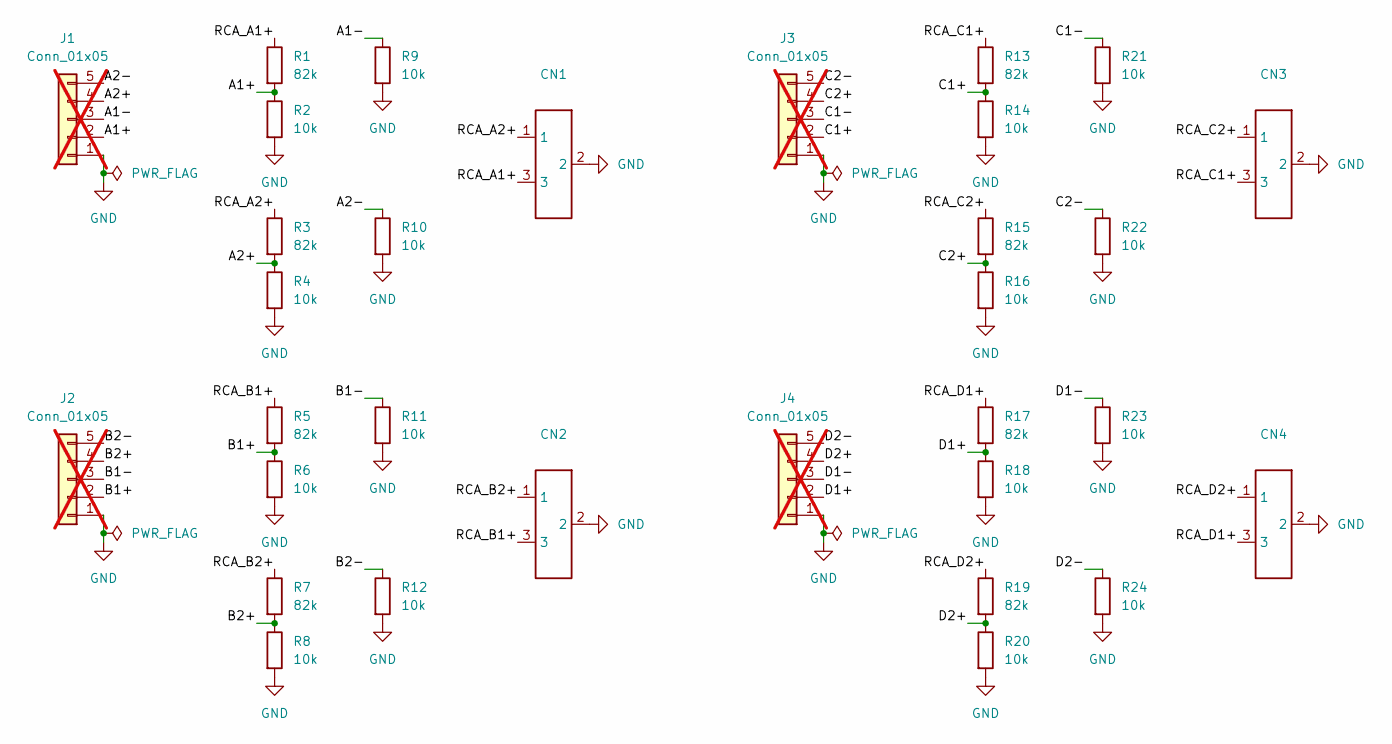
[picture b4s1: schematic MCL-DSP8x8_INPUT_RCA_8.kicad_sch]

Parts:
CN1, CN2, CN3, CN4: XDJK-0271-1650; Manufacturer Part XDJK-0271-1650; LCSC Part Name 双层莲花座
J1, J2, J3, J4: Conn_01x05; PinHeader_1x05_P2.54mm_Vertical; not fitted
R1, R3, R5, R7, R13, R15, R17, R19: 82k; R_0805_2012Metric_Pad1.20x1.40mm_HandSolder; LCSC Part # C22356755
R2, R4, R6, R8, R9, R10, R11, R12, R14, R16, R18, R20, R21, R22, R23, R24: 10k; R_0805_2012Metric_Pad1.20x1.40mm_HandSolder; LCSC Part # C3152175

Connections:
/A1+: J1.2, R1.2, R2.1
/A1-: J1.3, R9.1
/A2+: J1.4, R3.2, R4.1
/A2-: J1.5, R10.1
/B1+: J2.2, R5.2, R6.1
/B1-: J2.3, R11.1
/B2+: J2.4, R7.2, R8.1
/B2-: J2.5, R12.1
/C1+: J3.2, R13.2, R14.1
/C1-: J3.3, R21.1
/C2+: J3.4, R15.2, R16.1
/C2-: J3.5, R22.1
/D1+: J4.2, R17.2, R18.1
/D1-: J4.3, R23.1
/D2+: J4.4, R19.2, R20.1
/D2-: J4.5, R24.1
/RCA_A1+: CN1.3, R1.1
/RCA_A2+: CN1.1, R3.1
/RCA_B1+: CN2.3, R5.1
/RCA_B2+: CN2.1, R7.1
/RCA_C1+: CN3.3, R13.1
/RCA_C2+: CN3.1, R15.1
/RCA_D1+: CN4.3, R17.1
/RCA_D2+: CN4.1, R19.1
GND: CN1.2, CN2.2, CN3.2, CN4.2, J1.1, J2.1, J3.1, J4.1, R2.2, R4.2, R6.2, R8.2, R9.2, R10.2, R11.2, R12.2, R14.2, R16.2, R18.2, R20.2, R21.2, R22.2, R23.2, R24.2

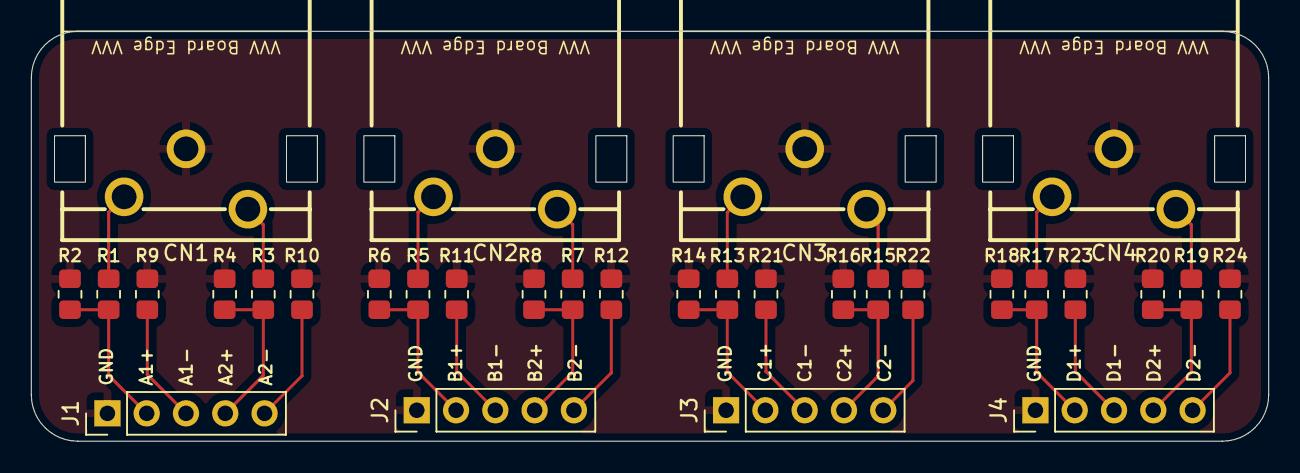
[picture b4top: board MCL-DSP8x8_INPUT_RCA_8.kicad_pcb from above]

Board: 2 copper layers, 80.0 x 26.5 mm, 32 parts (0 on the bottom side), 25 nets.

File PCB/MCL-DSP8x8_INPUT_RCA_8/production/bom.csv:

Designator,Footprint,Quantity,Value,LCSC Part #
"CN1, CN2, CN3, CN4",XDJK-0271-1650,4,~,C7527522
"R1, R13, R15, R17, R19, R3, R5, R7",0805,8,82k,C22356755
"R10, R11, R12, R14, R16, R18, R2, R20, R21, R22, R23, R24, R4, R6, R8, R9",0805,16,10k,C3152175

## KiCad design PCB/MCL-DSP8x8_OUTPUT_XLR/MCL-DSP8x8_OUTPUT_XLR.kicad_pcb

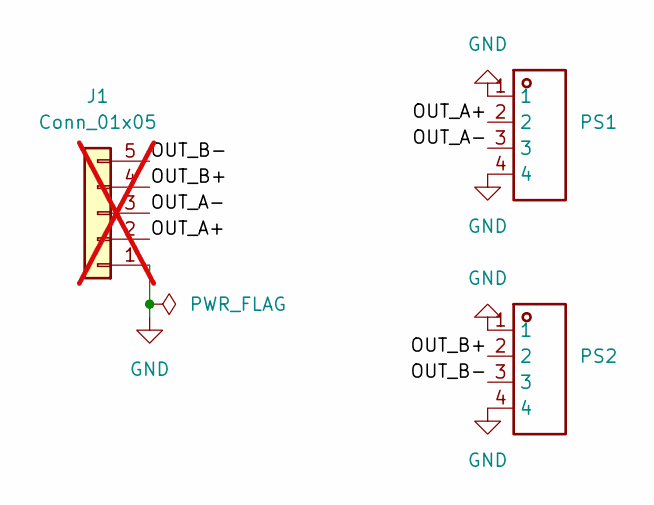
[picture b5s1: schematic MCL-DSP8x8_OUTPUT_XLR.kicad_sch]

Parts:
J1: Conn_01x05; PinHeader_1x05_P2.54mm_Vertical; not fitted
PS1, PS2: NC3MAAH-0; Manufacturer Part NC3MAAH-0; LCSC Part Name NC3MAAH-0

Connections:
/OUT_A+: J1.2, PS1.2
/OUT_A-: J1.3, PS1.3
/OUT_B+: J1.4, PS2.2
/OUT_B-: J1.5, PS2.3
GND: J1.1, PS1.1, PS1.4, PS2.1, PS2.4
